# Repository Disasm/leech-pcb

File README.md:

# Leech

An extension board with iCE40UP5k for the STM32F411 "Black Pill" board.

This project is based on the [icepill] project by [Adam Greig].
Some of the footprints were also taken from the icepill project.

| iCE40  | STM32 | Notes
|--------|-------|------
| 16     | PB12  | SPI SS
| 15     | PB13  | SPI SCK
| 14     | PB14  | SPI MISO
| 17     | PB15  | SPI MOSI
| 20     | PA8   | Clock for iCE40 provided by MCO
| 13     | PA9   |
| 12     | PA10  |
| 11     | PA11  |
| 10     | PA12  |
| 6      | PA15  |
| 3      | PB3   |
| 2      | PB4   |
| 48     | PB5   |
| 47     | PB6   |
| 46     | PB7   |
| 45     | PB8   |
| 44     | PB9   |
|        |       |
| 18     | PB10  | Used for IRQ
| CRESET | PB2   | This line is pulled down by the main board
| 25     | PB1   |
| 26     | PB0   |
| 27     | PA7   |
| 28     | PA6   |
| 34     | PA5   |
| 35     | PA4   |
| 36     | PA3   |
| 37     | PA2   |
| 38     | PA1   |
| 42     | PA0   | Connected to a button on the main board
| 43     | RESET |

Firmware and gateware: https://github.com/Disasm/leech-fw

This schematic and PCB design are licensed under the
Creative Commons [CC0 public domain dedication].
It is provided with no warranty.

[icepill]: https://github.com/adamgreig/icepill
[Adam Greig]: https://github.com/adamgreig
[CC0 public domain dedication]: https://creativecommons.org/publicdomain/zero/1.0/

## Revision History

### 1.2: 2020-11-13

* First version.
* Errata:
    * Drill diameter of 2.54mm connector pads is too small.

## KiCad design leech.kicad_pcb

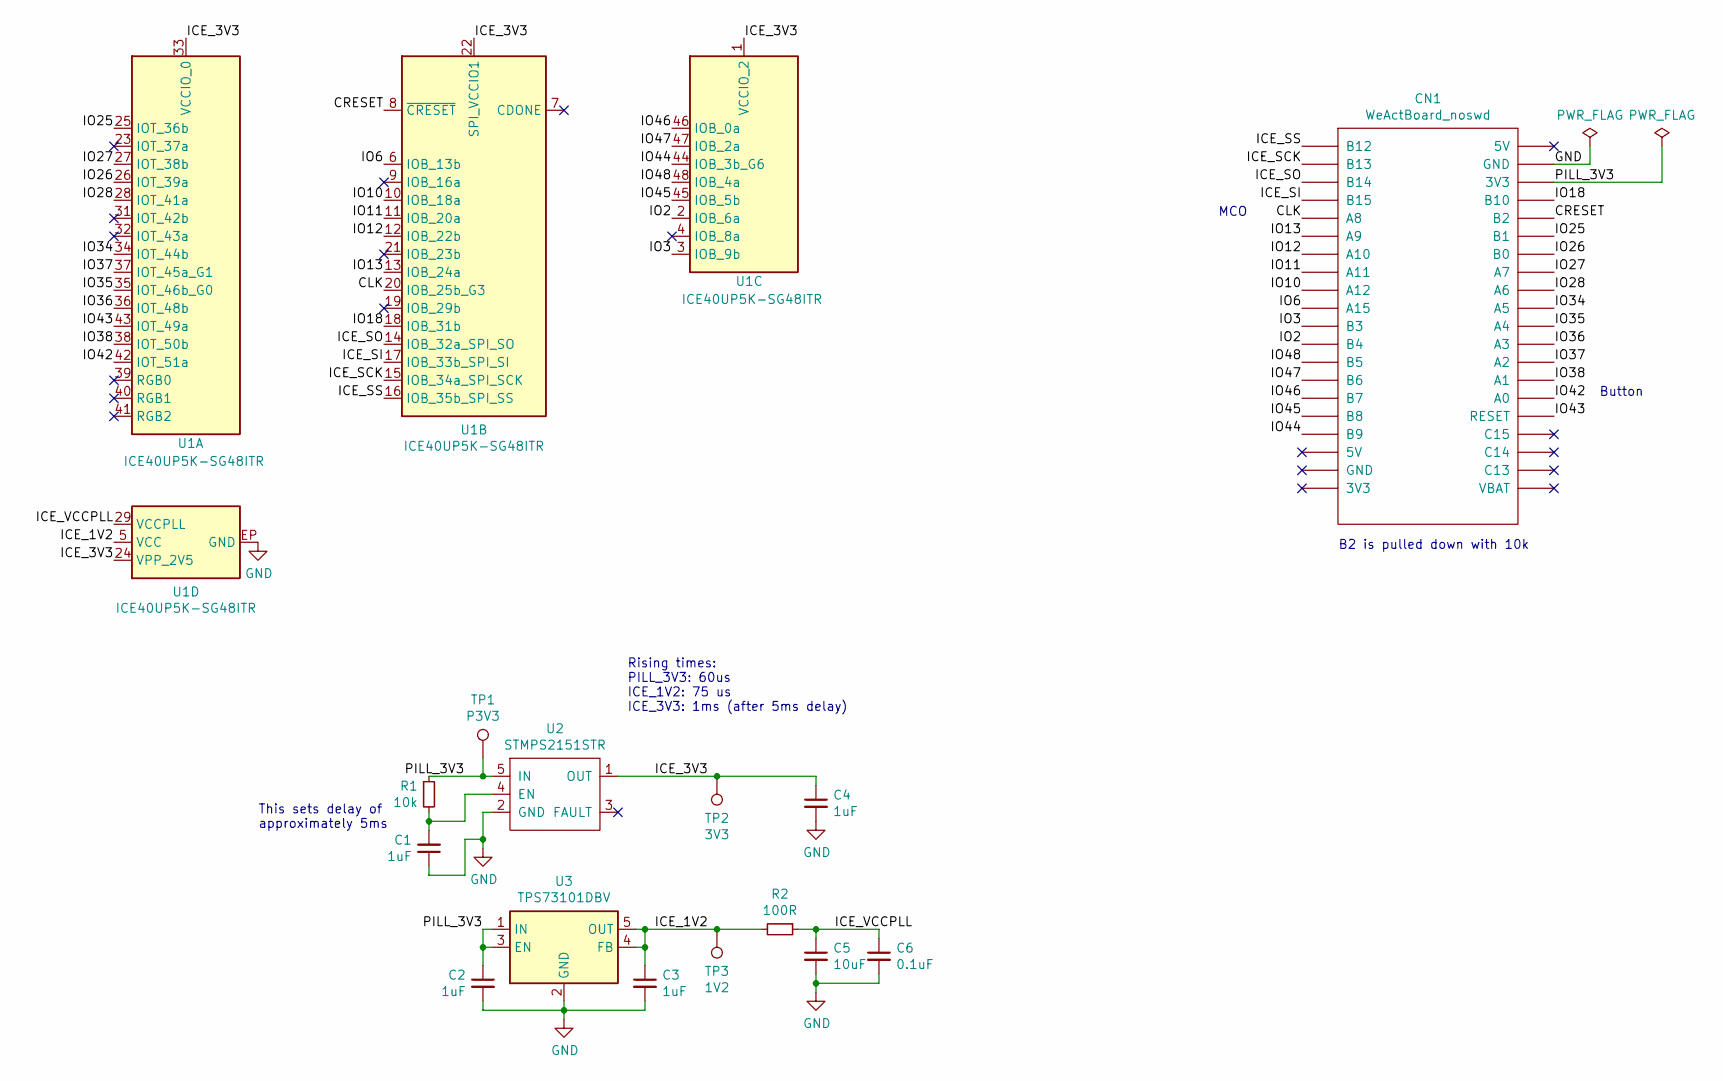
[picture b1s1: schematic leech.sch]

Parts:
C1, C2, C3, C4: 1uF; C_0805_2012Metric
C5: 10uF; C_0805_2012Metric
C6: 0.1uF; C_0805_2012Metric
CN1: WeActBoard_noswd; WeAct_v3.0_cut
R1: 10k; R_0805_2012Metric
R2: 100R; R_0805_2012Metric
TP1: P3V3; TestPoint_Pad_D1.0mm
TP2: 3V3; TestPoint_Pad_D1.0mm
TP3: 1V2; TestPoint_Pad_D1.0mm
U1: ICE40UP5K-SG48ITR; Lattice-SG48
U2: STMPS2151STR; SOT-23-5
U3: TPS73101DBV; SOT-23-5

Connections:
/CLK: CN1.5 (A8), U1.20 (IOB_25b_G3)
/CRESET: CN1.36 (B2), U1.8 (~CRESET)
/ICE_1V2: C3.1, R2.2, TP3.1, U1.5 (VCC), U1.30 (VCC), U3.4 (FB), U3.5 (OUT)
/ICE_3V3: C4.1, TP2.1, U1.1 (VCCIO_2), U1.22 (SPI_VCCIO1), U1.24 (VPP_2V5), U1.33 (VCCIO_0), U2.1 (OUT)
/ICE_SCK: CN1.2 (B13), U1.15 (IOB_34a_SPI_SCK)
/ICE_SI: CN1.4 (B15), U1.17 (IOB_33b_SPI_SI)
/ICE_SO: CN1.3 (B14), U1.14 (IOB_32a_SPI_SO)
/ICE_SS: CN1.1 (B12), U1.16 (IOB_35b_SPI_SS)
/ICE_VCCPLL: C5.1, C6.1, R2.1, U1.29 (VCCPLL)
/IO2: CN1.12 (B4), U1.2 (IOB_6a)
/IO3: CN1.11 (B3), U1.3 (IOB_9b)
/IO6: CN1.10 (A15), U1.6 (IOB_13b)
/IO10: CN1.9 (A12), U1.10 (IOB_18a)
/IO11: CN1.8 (A11), U1.11 (IOB_20a)
/IO12: CN1.7 (A10), U1.12 (IOB_22b)
/IO13: CN1.6 (A9), U1.13 (IOB_24a)
/IO18: CN1.37 (B10), U1.18 (IOB_31b)
/IO25: CN1.35 (B1), U1.25 (IOT_36b)
/IO26: CN1.34 (B0), U1.26 (IOT_39a)
/IO27: CN1.33 (A7), U1.27 (IOT_38b)
/IO28: CN1.32 (A6), U1.28 (IOT_41a)
/IO34: CN1.31 (A5), U1.34 (IOT_44b)
/IO35: CN1.30 (A4), U1.35 (IOT_46b_G0)
/IO36: CN1.29 (A3), U1.36 (IOT_48b)
/IO37: CN1.28 (A2), U1.37 (IOT_45a_G1)
/IO38: CN1.27 (A1), U1.38 (IOT_50b)
/IO42: CN1.26 (A0), U1.42 (IOT_51a)
/IO43: CN1.25 (RESET), U1.43 (IOT_49a)
/IO44: CN1.17 (B9), U1.44 (IOB_3b_G6)
/IO45: CN1.16 (B8), U1.45 (IOB_5b)
/IO46: CN1.15 (B7), U1.46 (IOB_0a)
/IO47: CN1.14 (B6), U1.47 (IOB_2a)
/IO48: CN1.13 (B5), U1.48 (IOB_4a)
/PILL_3V3: C2.1, CN1.38 (3V3), R1.1, TP1.1, U2.5 (IN), U3.1 (IN), U3.3 (EN)
GND: C1.1, C2.2, C3.2, C4.2, C5.2, C6.2, CN1.39 (GND), U1.EP (GND), U2.2 (GND), U3.2 (GND)
unnamed: C1.2, R1.2, U2.4 (EN)

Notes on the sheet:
B2 is pulled down with 10k
Button
MCO
This sets delay of approximately 5ms
Rising times: PILL_3V3: 60us ICE_1V2: 75 us ICE_3V3: 1ms (after 5ms delay)

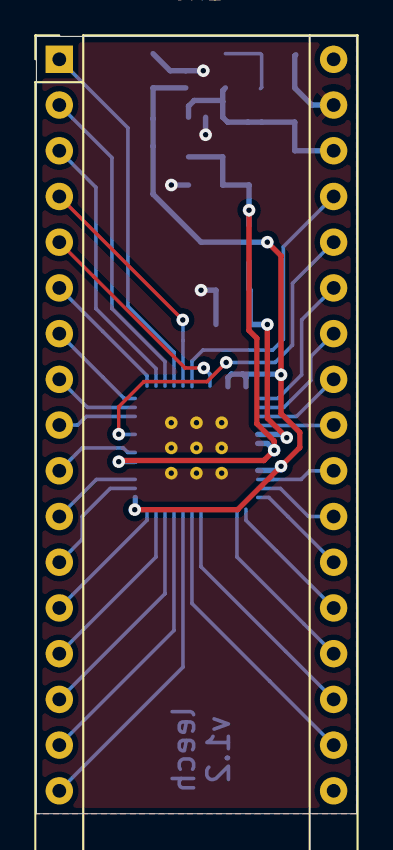
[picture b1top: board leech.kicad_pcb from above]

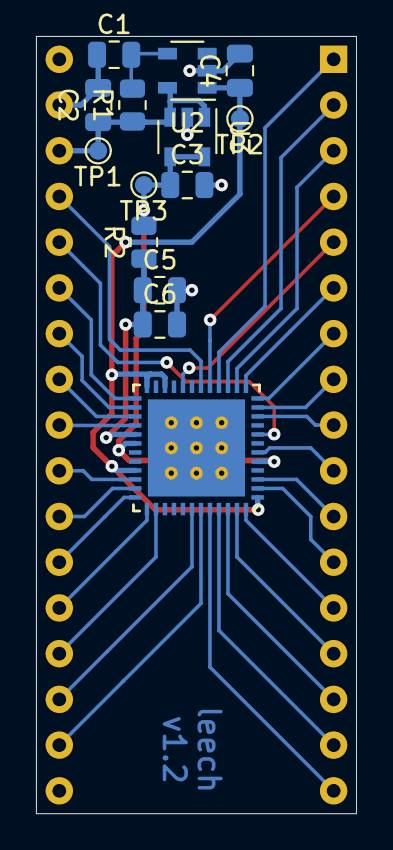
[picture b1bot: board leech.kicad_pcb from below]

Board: 2 copper layers, 17.8 x 43.2 mm, 15 parts (14 on the bottom side), 36 nets.

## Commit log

2020-11-12 Add .gitignore
2020-11-12 Add libs
2020-11-12 Add board schematics and layout
2020-11-12 Set solder mask params to zero to fix warning
2020-11-12 Prepare for Gerber generation
2020-11-12 Generate gerbers
2020-11-12 Remove soldermask under the ice40 footprint
2020-11-12 Bump board version (v1.1)
2020-11-12 Regenerate gerbers
2020-11-13 Revert "Set solder mask params to zero to fix warning"
    This reverts commit 59b1d9f25f2c3b17ac02e019903f67e575fe32d2.
2020-11-13 Update the iCE40 footprint to prevent 'half-covered vias' warning
2020-11-13 Update board version to 1.2, regenerate gerbers
2020-11-13 Add schematics pdf
2020-12-05 Add IBOM
2020-12-10 Add README.md
2020-12-10 Add firmware link
2020-12-10 Add pinout table
